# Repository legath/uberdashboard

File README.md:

# uberdashboard
Uberdashboard is the project for creating overengineered motorcycle dashboard.
It is starts from using two VID23-03 motors and 3.7" samsung amoled screen for good view on sunlight.

fw repo:
https://github.com/legath/uberdashboard-src

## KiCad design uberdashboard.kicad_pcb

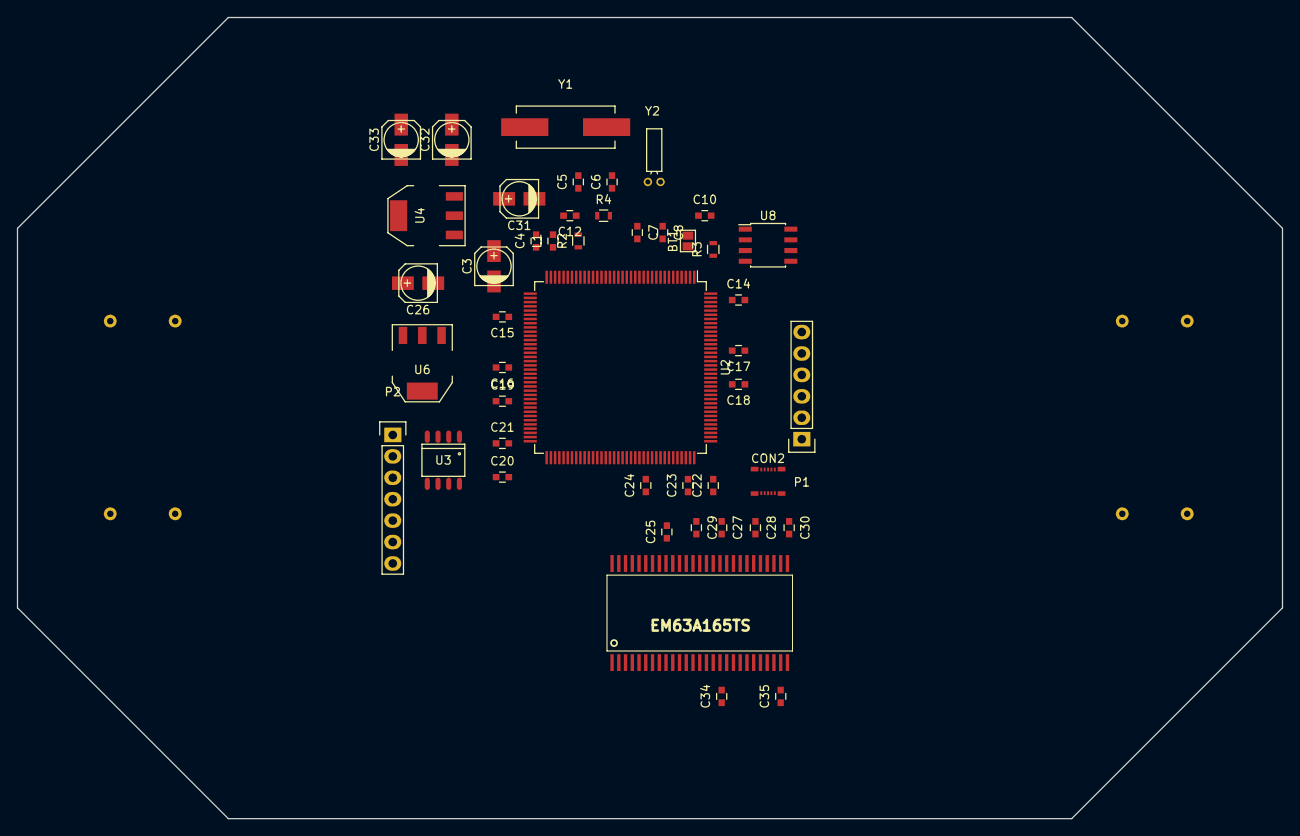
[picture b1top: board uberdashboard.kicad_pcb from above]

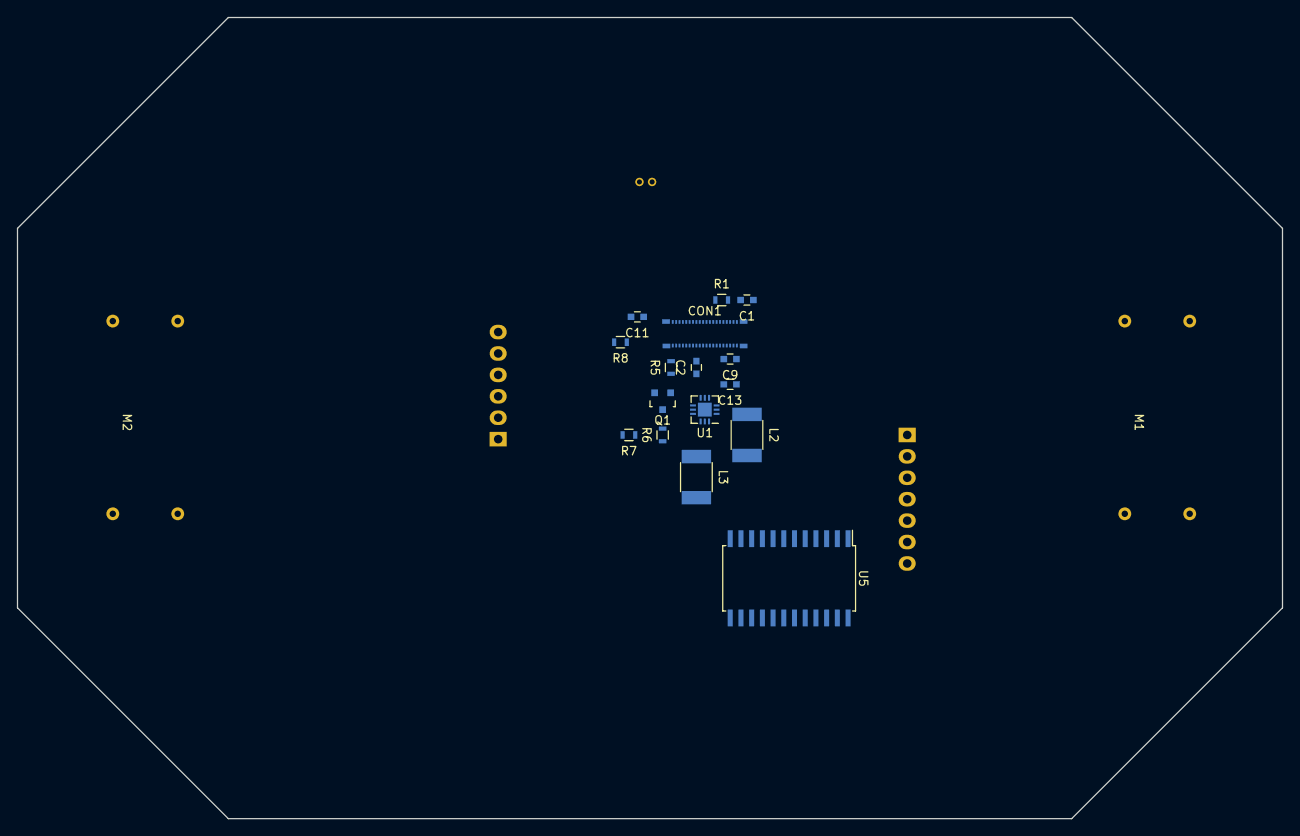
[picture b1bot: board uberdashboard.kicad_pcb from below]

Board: 2 copper layers, 150.0 x 95.0 mm, 64 parts (18 on the bottom side), 108 nets, no tracks yet.

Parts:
BT1: 3V; GS2
C1, C9, C13: 10uF; C_0603
C2: 1uF; C_0603
C3: 1uF; c_elec_4x5.8
C4: 100nF; C_0603
C5, C6: 20pF; C_0603
C7, C8, C10, C24, C25: C; C_0603
C11, C12, C14, C15, C16, C17, C18, C19, C20, C22, C27, C28, C29, C30, C34, C35: 0.1uF; C_0603
C21, C23: 2.2uF; C_0603
C26, C31, C32, C33: 10uF; c_elec_4x5.3
CON1: AMOLED-BM10NB(0.8)-40DS-0.4V(51); BM10NB(0.8)-40DS-0.4V(51)
CON2: TOUCH-BM10NB(0.8)-10DS-0.4V(51); BM10NB(0.8)-10DS-0.4V(51)
L1: INDUCTOR; C_0603
L2, L3: 4.7uH; R_1812
M1, M2: VID23-03; VID23
P1: CONN_01X06; Pin_Header_Straight_1x06
P2: CONN_ROUNDX07; Pin_Header_Straight_1x07
Q1: BC817-40; SOT-23
R1, R6: 10K; R_0603
R2: 10k; R_0603
R3: 0; R_0603
R4: 220; R_0603
R5: 1K; R_0603
R7, R8: 4.7k; R_0603
U1: STOD13AS; QFN-12-1EP_3x3mm_Pitch0.5mm
U2: STM32F429ZIT6; LQFP-144_20x20mm_Pitch0.5mm
U3: MCP2551-I/SN; SO-8
U4: LD1117S50TR; SOT-223
U5: PCA9555; SOIC-24_7.5x15.4mm_Pitch1.27mm
U6: LD1117S33TR; SOT-223
U7: EM63A165TS; TSOP54
U8: MX25L3206E; SOIC-8_3.9x4.9mm_Pitch1.27mm
Y1: 8MHz; Crystal_HC49-SD_SMD
Y2: 32 kHz; Crystal_Round_Horizontal_2mm

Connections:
+5V: C31.1, CON2.3, CON2.5, P2.1, U3.3, U4.2, U5.24
+12V: C26.1, C32.1, U4.3, U6.3
/A0: U2.10, U7.23
/A1: U2.11, U7.24
/A2: U2.12, U7.25
/A3: U2.13, U7.26
/A4: U2.14, U7.29
/A5: U2.15, U7.30
/A6: U2.50, U7.31
/A7: U2.53, U7.32
/A8: U2.54, U7.33
/A9: U2.55, U7.34
/A10: U2.56, U7.22
/A11: U2.57, U7.35
/A12: U2.87, U7.36
/B0: CON1.34, U2.122
/B1: CON1.33, U2.126
/B2: CON1.32, U2.127
/B3: CON1.31, U2.37
/B4: CON1.30, U2.139
/B5: CON1.29, U2.140
/BA0: U2.89, U7.20
/BA1: U2.90, U7.21
/CAS#: U2.132, U7.17
/CKE: U2.135, U7.37
/CLK: U2.93, U7.38
/CS#: U2.136, U7.19
/CSB: CON1.37, U2.45
/D0: U2.85, U7.2
/D1: U2.86, U7.4
/D2: U2.114, U7.5
/D3: U2.115, U7.7
/D4: U2.58, U7.8
/D5: U2.59, U7.10
/D6: U2.60, U7.11
/D7: U2.63, U7.13
/D8: U2.64, U7.42
/D9: U2.65, U7.44
/D10: U2.66, U7.45
/D11: U2.67, U7.47
/D12: U2.68, U7.48
/D13: U2.77, U7.50
/D14: U2.78, U7.51
/D15: U2.79, U7.53
/EN: CON1.12, U2.22
/G0: CON1.28, U2.42
/G1: CON1.27, U2.125
/G2: CON1.26, U2.69
/G3: CON1.25, U2.70
/G4: CON1.24, U2.97
/G5: CON1.23, U2.117
/HSYNC: CON1.9, U2.96
/IRQ: CON2.9, U2.101
/MISO: U2.4, U8.2
/MOSI: U2.5, U8.5
/NBL0: U2.141, U7.15
/NBL1: U2.142, U7.39
/NSS: U2.3, U8.1
/PCLK: CON1.8, U2.92
/R0: CON1.22, U2.111
/R1: CON1.21, U2.46
/R2: CON1.20, U2.103
/R3: CON1.19, U2.104
/R4: CON1.18, U2.47
/R5: CON1.17, U2.91
/RAS#: U2.49, U7.18
/RESETB: CON1.15, U2.48
/SCK: U2.1, U8.6
/SCL: CON1.40, CON2.7, R8.2, U2.20, U2.100, U5.22
/SDA: CON2.8, R7.2, U2.99, U5.23
/SDI: CON1.35, U2.21
/VSYNC: CON1.11, U2.40
/WE#: U2.26, U7.16
GND: BT1.2, C1.2, C2.2, C3.2, C4.2, C5.2, C6.2, C7.2, C8.2, C9.2, C10.1, C11.1, C12.2, C13.2, C14.2, C15.2, C16.2, C17.1, C18.1, C19.1, C20.1, C21.1, C22.1, C23.1, C24.1, C25.1, C26.2, C27.2, C28.2, C29.2, C30.2, C31.2, C32.2, C33.2, C34.1, C35.1, CON1.6, CON1.10, CON1.14, CON1.38, CON1.39, CON2.1, CON2.6, CON2.10, L3.2, P1.3, P2.6, Q1.2, R1.2, U1.2, U1.5, U1.13, U2.16, U2.31, U2.38, U2.51, U2.61, U2.83, U2.94, U2.107, U2.120, U2.130, U2.138, U3.2, U3.8, U4.1, U5.2, U5.3, U5.12, U5.21, U6.1, U7.6, U7.12, U7.28, U7.41, U7.46, U7.52, U7.54, U8.4
unnamed: BT1.1, C10.2, R3.2, U2.6
unnamed: C1.1, CON1.1, CON1.3, U1.3
unnamed: C2.1, U1.6
unnamed: C3.1, C4.1, L1.1, U2.33
unnamed: C5.1, U2.23, Y1.1
unnamed: C6.1, R4.2, Y1.2
unnamed: C7.1, U2.8, Y2.1
unnamed: C8.1, U2.9, Y2.2
unnamed: C9.1, C13.1, CON1.2, CON1.4, U1.9
unnamed: C21.2, U2.71
unnamed: C23.2, U2.106
unnamed: CON1.13, R1.1
unnamed: CON1.36, R5.2
unnamed: L2.1, U1.1
unnamed: L3.1, U1.10
unnamed: M1.1, U5.4
unnamed: M1.2, U5.5
unnamed: M1.3, U5.6
unnamed: M1.4, U5.7
unnamed: M2.1, U5.13
unnamed: M2.2, U5.14
unnamed: M2.3, U5.15
unnamed: M2.4, U5.16
unnamed: P1.2, U2.109
unnamed: P1.4, U2.105
unnamed: P1.5, R2.1, U2.25
unnamed: P2.2, U3.7
unnamed: P2.7, U3.6
unnamed: Q1.1, R5.1
unnamed: Q1.3, R6.2, U1.8
unnamed: R4.1, U2.24
unnamed: U2.73, U3.4
unnamed: U2.74, U3.1
VDD: C11.2, C12.1, C14.1, C15.1, C16.1, C17.2, C18.2, C19.2, C20.2, C22.2, C24.2, C25.2, C27.1, C28.1, C29.1, C30.1, C33.1, C34.2, C35.2, CON1.5, CON1.7, CON1.16, L1.2, L2.2, P1.1, R2.2, R3.1, R6.1, R7.1, R8.1, U1.11, U1.12, U2.17, U2.30, U2.39, U2.52, U2.62, U2.72, U2.84, U2.95, U2.108, U2.121, U2.131, U2.143, U2.144, U6.2, U7.1, U7.3, U7.9, U7.14, U7.27, U7.43, U7.49, U8.3, U8.7, U8.8

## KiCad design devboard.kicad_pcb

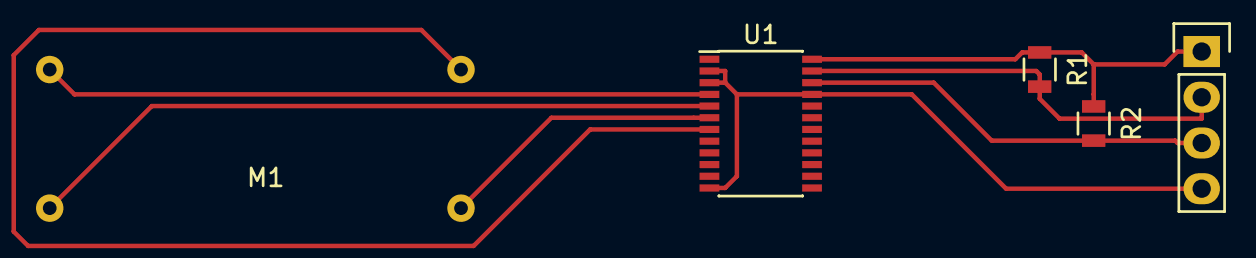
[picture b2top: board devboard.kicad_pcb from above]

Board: 2 copper layers, 5 parts (0 on the bottom side), 8 nets.

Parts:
M1: VID23-03; VID23
P1: CONN_01X04; Pin_Header_Straight_1x04
R1, R2: R; R_0805
U1: PCA9555; TSSOP-24_4.4x7.8mm_Pitch0.65mm

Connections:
+5V: P1.1, R1.1, R2.1, U1.24
GND: P1.4, U1.2, U1.3, U1.12, U1.21
unnamed: M1.1, U1.4
unnamed: M1.2, U1.5
unnamed: M1.3, U1.6
unnamed: M1.4, U1.7
unnamed: P1.2, R1.2, U1.23
unnamed: P1.3, R2.2, U1.22

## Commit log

2015-12-23 Let s starts
2015-12-23 test
2015-12-23 outputs
2015-12-23 finished stm32f429 schematic component
2015-12-29 New components in library and on schematic
2015-12-29 VID23-03 in library
2016-01-12 Starts sdram connecting and separated list for motors
2016-01-13 Edit readme
2016-01-13 Power implementation and finish ram bus implementation
2016-01-13 changed can tranciever
2016-01-13 Starts lcd-bus drawing
2016-01-14 Finished screen connection and reannotation
2016-01-14 Flash bus implementation
2016-01-14 ext connector and speed motor
2016-01-18 motors
2016-01-18 BM10NB(0.8)-40DS-0.4V(51)
2016-01-19 packages
2016-01-19 netlist
2016-01-19 doc library
2016-01-19 Update README.md
    mistake
2016-01-19 touch connection
2016-01-22 starts routing
2016-02-05 new case
2016-02-12 f*cked grid
2016-02-15 ram bus redrawed
2016-02-15 CAN redrawed
2016-02-16 port expander changed to PCA9555
2016-02-16 motor and touch and screen redrawed
2016-02-17 g2 g3 fix
2016-02-17 single i2c bus
2016-02-19 copyed battery symbol
2016-02-19 power pins
2016-03-15 swd added
2016-03-15 C on CPU and RAM
2016-03-15 devboard and NRST on main board
2016-03-15 fw repo comment
2016-03-20 Added files via upload
2016-03-21 Revert "devboard and NRST on main board"
    This reverts commit f0b69f0e92652c3e00bd8a39b39132af0288dba0.
2016-03-21 right export
2016-03-21 regeneraed netlist
2016-03-23 i2c to vdd
2016-03-23 reannotation and removed unncessary R
2016-03-28 misplaced
2016-04-04 Touch connector
